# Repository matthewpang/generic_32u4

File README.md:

# generic_32u4
Generic Atmel 32u4 Board

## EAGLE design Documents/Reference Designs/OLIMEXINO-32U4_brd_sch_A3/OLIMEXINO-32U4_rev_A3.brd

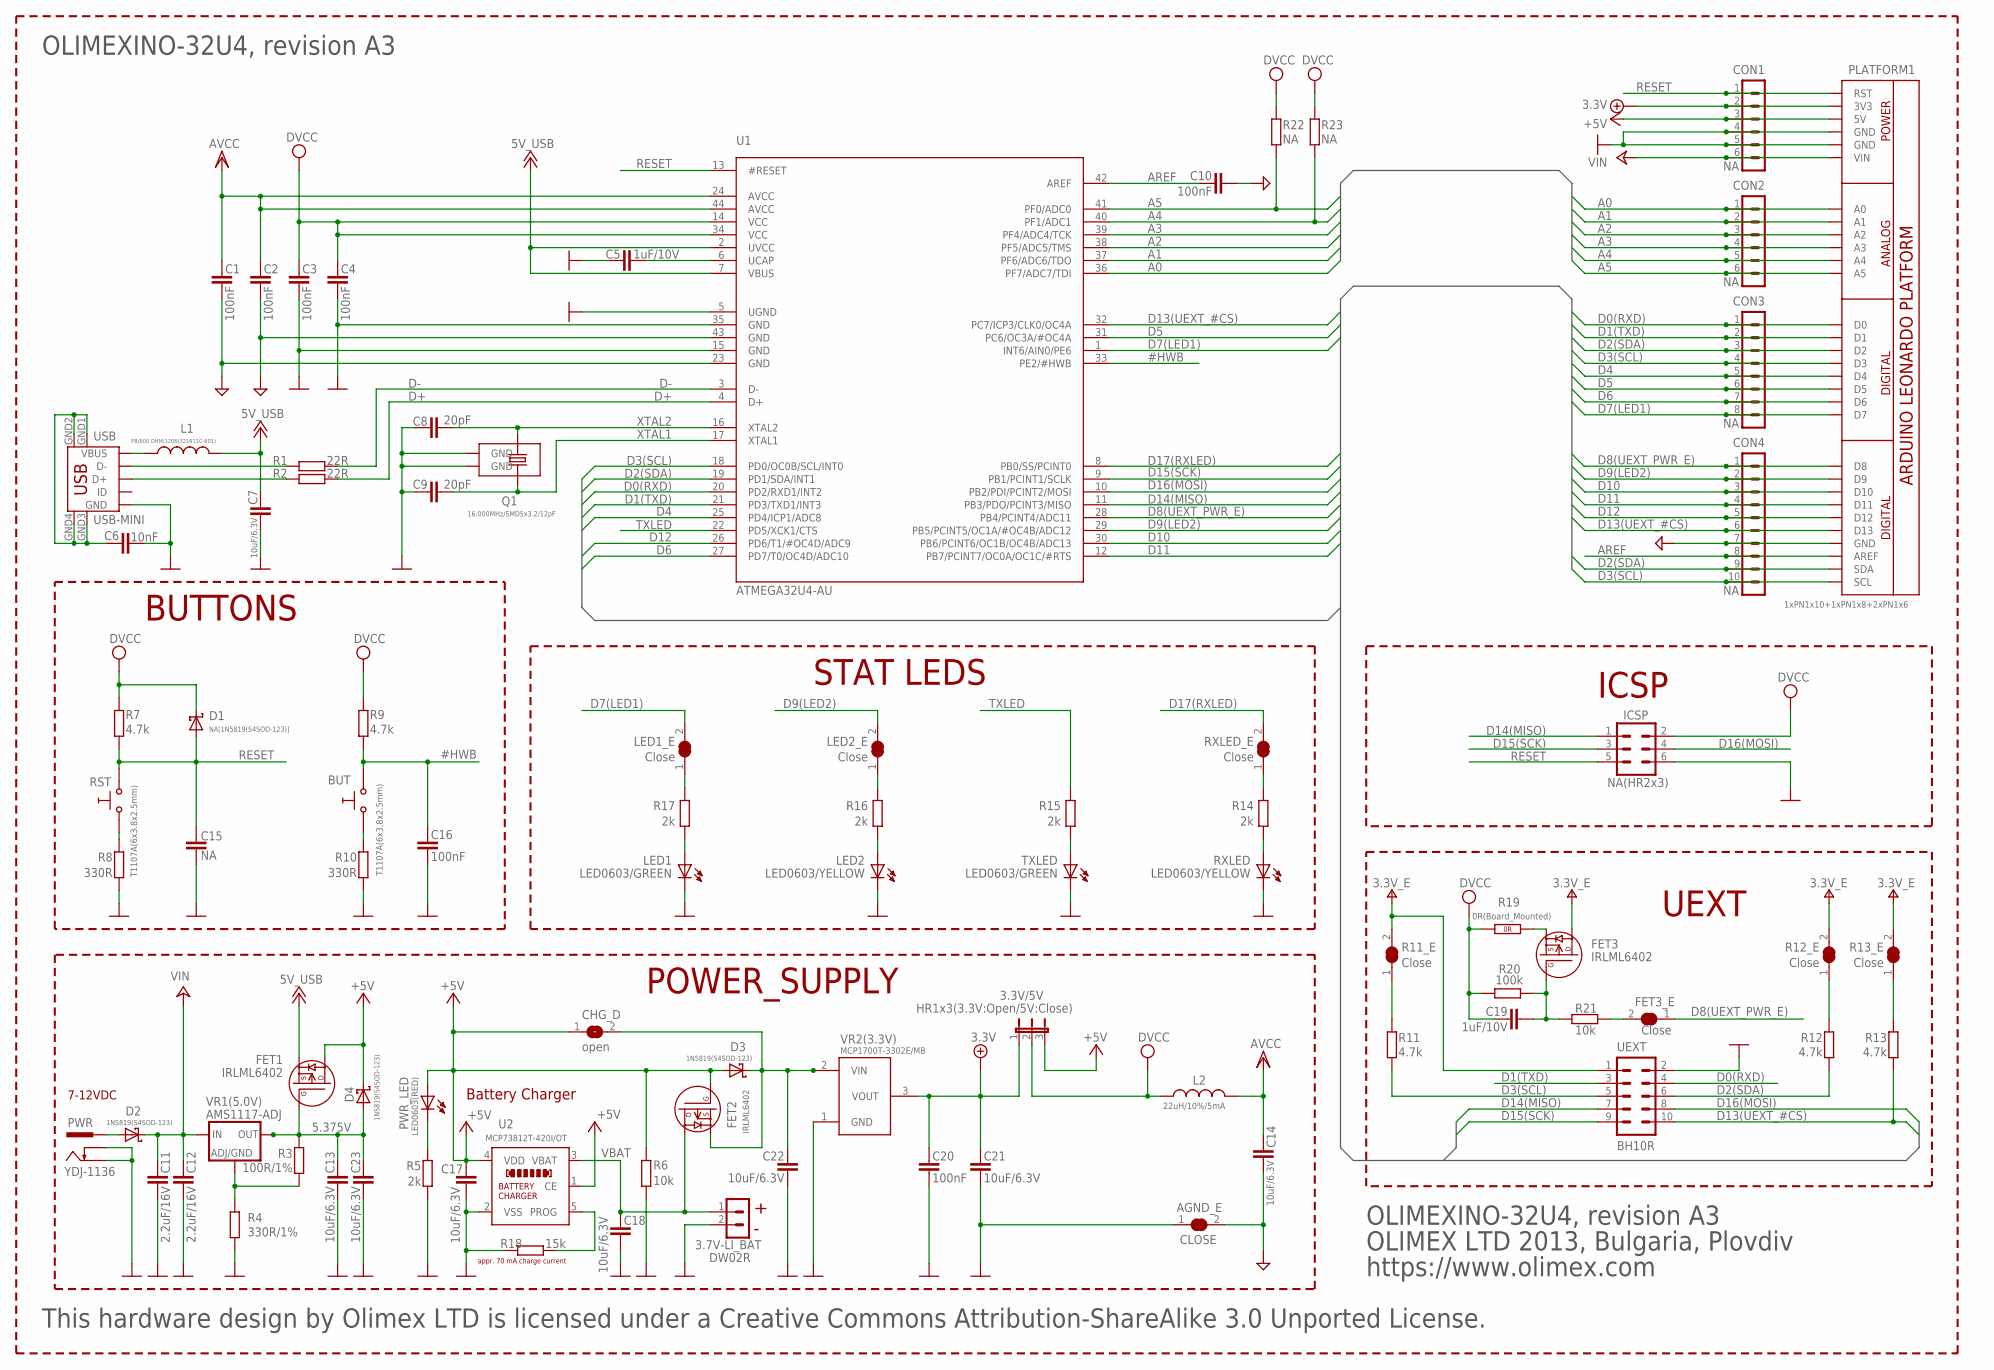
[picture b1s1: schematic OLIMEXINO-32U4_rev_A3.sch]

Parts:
3.3V/5V: HR1x3(3.3V:Open/5V:Close); HR1X3
3.7V-LI_BAT: DW02R
AGND_E: CLOSE; SJ_1_SMALLER_CLOSE
BUT: T1107A(6x3.8x2.5mm); SW-TAKT_6X3.5_SMD
C1, C2, C3, C4, C10, C16, C20: 100nF; C0603_DWS
C5, C19: 1uF/10V; C0603_DWS
C6: 10nF; C0603_DWS
C7, C13, C14, C17, C18, C21, C22, C23: 10uF/6.3V; C0603_DWS
C8, C9: 20pF; C0603_DWS
C11, C12: 2.2uF/16V; C0805_5MIL_DWS
C15: NA; C0603_DWS
CHG_D: open; SJ_1_SMALLER
CON1, CON2: NA; HN1X6
CON3: NA; HN1X8
CON4: NA; HN1X10
D1: NA[1N5819(S4SOD-123)]; SOD-123
D2, D3, D4: 1N5819(S4SOD-123); SOD-123
FET1, FET2, FET3: IRLML6402; SOT23
FET3_E: Close; SJ_1_SMALLER_CLOSE
ICSP: NA(HR2x3); HN2X3R
L1: FB/600 OHM/1206(321611C-601); L3216C
L2: 22uH/10%/5mA; L3216C
LED1: LED0603/GREEN; LED-0603
LED1_E, LED2_E: Close; SJ_1_SMALLER_CLOSE
LED2: LED0603/YELLOW; LED-0603
PLATFORM1: 1xPN1x10+1xPN1x8+2xPN1x6; ARDUINO-LEONARDO-PLATFORM
PWR: YDJ-1136; PWR_JACK_UNI_MILLING
PWR_LED: LED0603(RED); LED-0603
Q1: 16.000MHz/SMD5x3.2/12pF; CRYSTAL_SMD
R1, R2: 22R; R0603_5MIL_DWS
R3: 100R/1%; R0603_5MIL_DWS
R4: 330R/1%; R0603_5MIL_DWS
R5, R14, R15, R16, R17: 2k; R0603_5MIL_DWS
R6, R21: 10k; R0603_5MIL_DWS
R7, R9, R11, R12, R13: 4.7k; R0603_5MIL_DWS
R8, R10: 330R; R0603_5MIL_DWS
R11_E, R12_E, R13_E: Close; SJ_1_SMALLER_CLOSE
R18: 15k; R0603_5MIL_DWS
R19: 0R(Board_Mounted); 0603_0R
R20: 100k; R0603_5MIL_DWS
R22, R23: NA; R0603_5MIL_DWS
RST: T1107A(6x3.8x2.5mm); SW-TAKT_6X3.5_SMD
RXLED: LED0603/YELLOW; LED-0603
RXLED_E: Close; SJ_1_SMALLER_CLOSE
TXLED: LED0603/GREEN; LED-0603
U1: ATMEGA32U4-AU; TQFP44
U2: MCP73812T-420I/OT; SOT-23-5
UEXT: BH10R
USB: USB-MINI; USB_MINI_9PIN
VR1(5.0V): AMS1117-ADJ; SOT223
VR2(3.3V): MCP1700T-3302E/MB; SOT89_REP_THERMALOFF

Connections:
3.3V_REG_IN: C22.1, CHG_D.2, D3.C, FET2.2 (S), VR2(3.3V).2 (VIN), VR2(3.3V).P$2 (VIN1)
5.375V: C13.1, C23.1, D4.A, FET1.1 (G), R3.2, VR1(5.0V).2 (OUT), VR1(5.0V).4 (RAD)
#HWB: BUT.P$2 (1), C16.1, R9.2, U1.33 (PE2/#HWB)
+5V: 3.3V/5V.3, C17.1, CHG_D.1, CON1.3, D3.A, D4.C, FET1.3 (D), FET2.1 (G), PLATFORM1.5V, PWR_LED.A, R6.1, U2.1 (CE), U2.4 (VDD)
+5V/1: 3.3V/5V.1, C20.1, C21.1, CON1.2, PLATFORM1.3V3, VR2(3.3V).3 (VOUT)
+12V: C7.1, FET1.2 (S), L1.2, U1.2 (UVCC), U1.7 (VBUS)
+24V: C11.1, C12.1, CON1.6, D2.C, PLATFORM1.VIN, VR1(5.0V).3 (IN)
A0: CON2.1, PLATFORM1.A0, U1.36 (PF7/ADC7/TDI)
A1: CON2.2, PLATFORM1.A1, U1.37 (PF6/ADC6/TDO)
A2: CON2.3, PLATFORM1.A2, U1.38 (PF5/ADC5/TMS)
A3: CON2.4, PLATFORM1.A3, U1.39 (PF4/ADC4/TCK)
A4: CON2.5, PLATFORM1.A4, R23.1, U1.40 (PF1/ADC1)
A5: CON2.6, PLATFORM1.A5, R22.1, U1.41 (PF0/ADC0)
AGND: AGND_E.2, C1.2, C2.2, C10.2, C14.2, CON4.7, PLATFORM1.GND@2 (GND), U1.23 (GND), U1.43 (GND)
AREF: C10.1, CON4.8, PLATFORM1.AREF, U1.42 (AREF)
D0(RXD): CON3.1, PLATFORM1.D0, U1.20 (PD2/RXD1/INT2), UEXT.4
D1(TXD): CON3.2, PLATFORM1.D1, U1.21 (PD3/TXD1/INT3), UEXT.3
D2(SDA): CON3.3, CON4.9, PLATFORM1.D2, PLATFORM1.SDA, R12.1, U1.19 (PD1/SDA/INT1), UEXT.6
D3(SCL): CON3.4, CON4.10, PLATFORM1.D3, PLATFORM1.SCL, R11.1, U1.18 (PD0/OC0B/SCL/INT0), UEXT.5
D4: CON3.5, PLATFORM1.D4, U1.25 (PD4/ICP1/ADC8)
D5: CON3.6, PLATFORM1.D5, U1.31 (PC6/OC3A/#OC4A)
D6: CON3.7, PLATFORM1.D6, U1.27 (PD7/T0/OC4D/ADC10)
D7(LED1): CON3.8, LED1_E.2, PLATFORM1.D7, U1.1 (INT6/AIN0/PE6)
D8(UEXT_PWR_E): CON4.1, FET3_E.1, PLATFORM1.D8, U1.28 (PB4/PCINT4/ADC11)
D9(LED2): CON4.2, LED2_E.2, PLATFORM1.D9, U1.29 (PB5/PCINT5/OC1A/#OC4B/ADC12)
D10: CON4.3, PLATFORM1.D10, U1.30 (PB6/PCINT6/OC1B/OC4B/ADC13)
D11: CON4.4, PLATFORM1.D11, U1.12 (PB7/PCINT7/OC0A/OC1C/#RTS)
D12: CON4.5, PLATFORM1.D12, U1.26 (PD6/T1/#OC4D/ADC9)
D13(UEXT_#CS): CON4.6, PLATFORM1.D13, R13.1, U1.32 (PC7/ICP3/CLK0/OC4A), UEXT.10
D14(MISO): ICSP.1, U1.11 (PB3/PDO/PCINT3/MISO), UEXT.7
D15(SCK): ICSP.3, U1.9 (PB1/PCINT1/SCLK), UEXT.9
D16(MOSI): ICSP.4, U1.10 (PB2/PDI/PCINT2/MOSI), UEXT.8
D17(RXLED): RXLED_E.2, U1.8 (PB0/SS/PCINT0)
D+: R2.2, U1.4 (D+)
D-: R1.2, U1.3 (D-)
GND: 3.7V-LI_BAT.2, AGND_E.1, C3.2, C4.2, C5.1, C6.2, C7.2, C8.1, C9.1, C11.2, C12.2, C13.2, C15.2, C16.2, C17.2, C18.2, C20.2, C21.2, C22.2, C23.2, CON1.4, CON1.5, ICSP.6, LED1.C, LED2.C, PLATFORM1.GND, PLATFORM1.GND@1 (GND), PWR.-, PWR.--, Q1.NC_1 (GND), Q1.NC_2 (GND), R4.1, R5.2, R6.2, R8.1, R10.1, R18.1, RXLED.C, TXLED.C, U1.5 (UGND), U1.15 (GND), U1.35 (GND), U2.2 (VSS), UEXT.2, USB.GND, VR2(3.3V).1 (GND)
unnamed: R1.1, USB.D-
unnamed: R14.2, RXLED_E.1
unnamed: R2.1, USB.D+
unnamed: R11.2, R11_E.1
unnamed: R15.1, TXLED.A
unnamed: FET3_E.2, R21.2
unnamed: R13.2, R13_E.1
unnamed: LED1.A, R17.1
unnamed: R8.2, RST.P$2 (1)
unnamed: BUT.P$1 (0), R10.2
unnamed: R12.2, R12_E.1
unnamed: LED1_E.1, R17.2
unnamed: D2.A, PWR.+
unnamed: LED2.A, R16.1
unnamed: LED2_E.1, R16.2
unnamed: C19.2, FET3.1 (G), R20.2, R21.1
unnamed: FET3.2 (S), R19.2 (1.2)
unnamed: PWR_LED.C, R5.1
unnamed: R18.2, U2.5 (PROG)
unnamed: R14.1, RXLED.A
unnamed: C6.1, USB.GND1, USB.GND2, USB.GND3, USB.GND4
RESET: C15.1, CON1.1, D1.A, ICSP.5, PLATFORM1.RST, R7.2, RST.P$1 (0), U1.13 (#RESET)
TXLED: R15.2, U1.22 (PD5/XCK1/CTS)
UCAP: C5.2, U1.6 (UCAP)
V+: FET3.3 (D), R11_E.2, R12_E.2, R13_E.2, UEXT.1
VBAT: 3.7V-LI_BAT.1, C18.1, FET2.3 (D), U2.3 (VBAT)
VBUS: L1.1, USB.VBUS
VCC: 3.3V/5V.2, C3.1, C4.1, C19.1, D1.C, ICSP.2, L2.1, R7.1, R9.1, R19.1 (1.1), R20.1, R22.2, R23.2, U1.14 (VCC), U1.34 (VCC)
VDD: C1.1, C2.1, C14.1, L2.2, U1.24 (AVCC), U1.44 (AVCC)
VR1_ADJ: R3.1, R4.2, VR1(5.0V).1 (ADJ/GND)
XTAL1: C9.2, Q1.1, U1.17 (XTAL1)
XTAL2: C8.2, Q1.2, U1.16 (XTAL2)

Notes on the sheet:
BUTTONS
STAT LEDS
UEXT
ICSP
7-12VDC
POWER_SUPPLY
Battery Charger
appr. 70 mA charge current
OLIMEXINO-32U4, revision A3
https://www.olimex.com
OLIMEX LTD 2013, Bulgaria, Plovdiv
This hardware design by Olimex LTD is licensed under a Creative Commons Attribution-ShareAlike 3.0 Unported License.

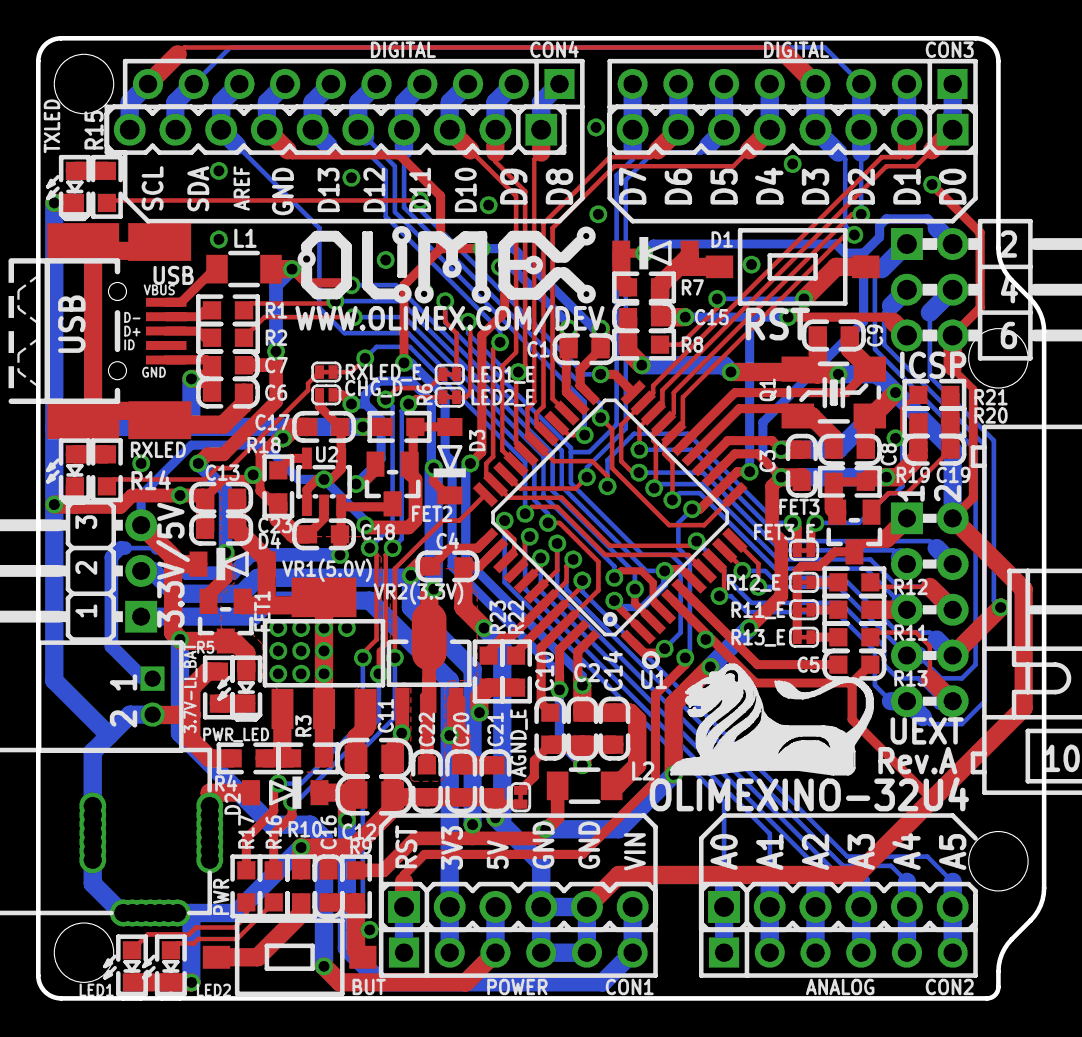
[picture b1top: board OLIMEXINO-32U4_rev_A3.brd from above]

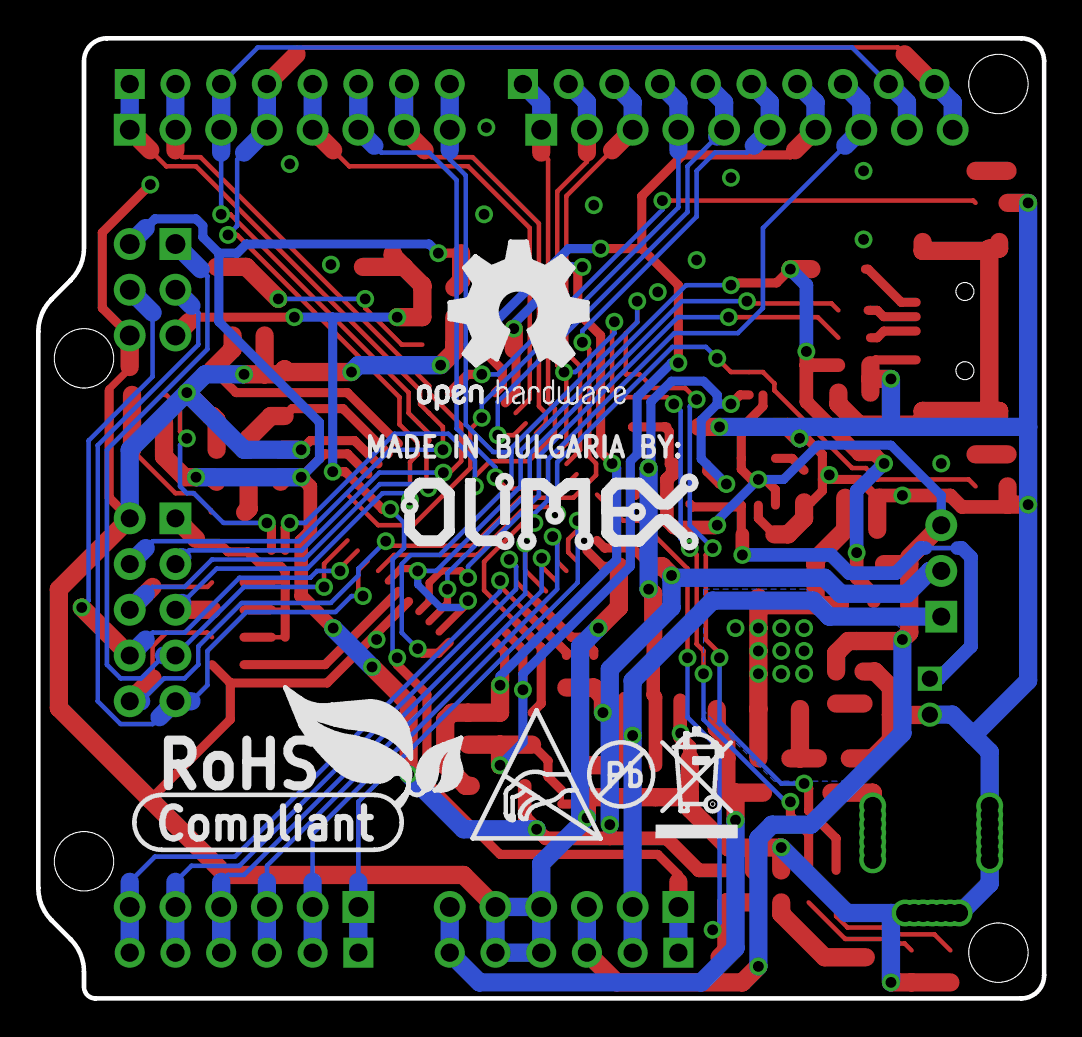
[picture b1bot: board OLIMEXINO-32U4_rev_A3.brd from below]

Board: 2 copper layers, 55.9 x 53.3 mm, 95 parts (6 on the bottom side), 68 nets.

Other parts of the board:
U$1: RECYCLE_BIN1/8
U$2: PB_SMALL
U$3: LOGO-OPENHARDWARE_8X8
U$8: ROHS
U$9, U$12: OLIMEX1_V
U$10: LION_12X7MM
U$11: ESD_SYMBOL

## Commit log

2016-05-14 Initial Commit :)
2016-05-14 cleanup
